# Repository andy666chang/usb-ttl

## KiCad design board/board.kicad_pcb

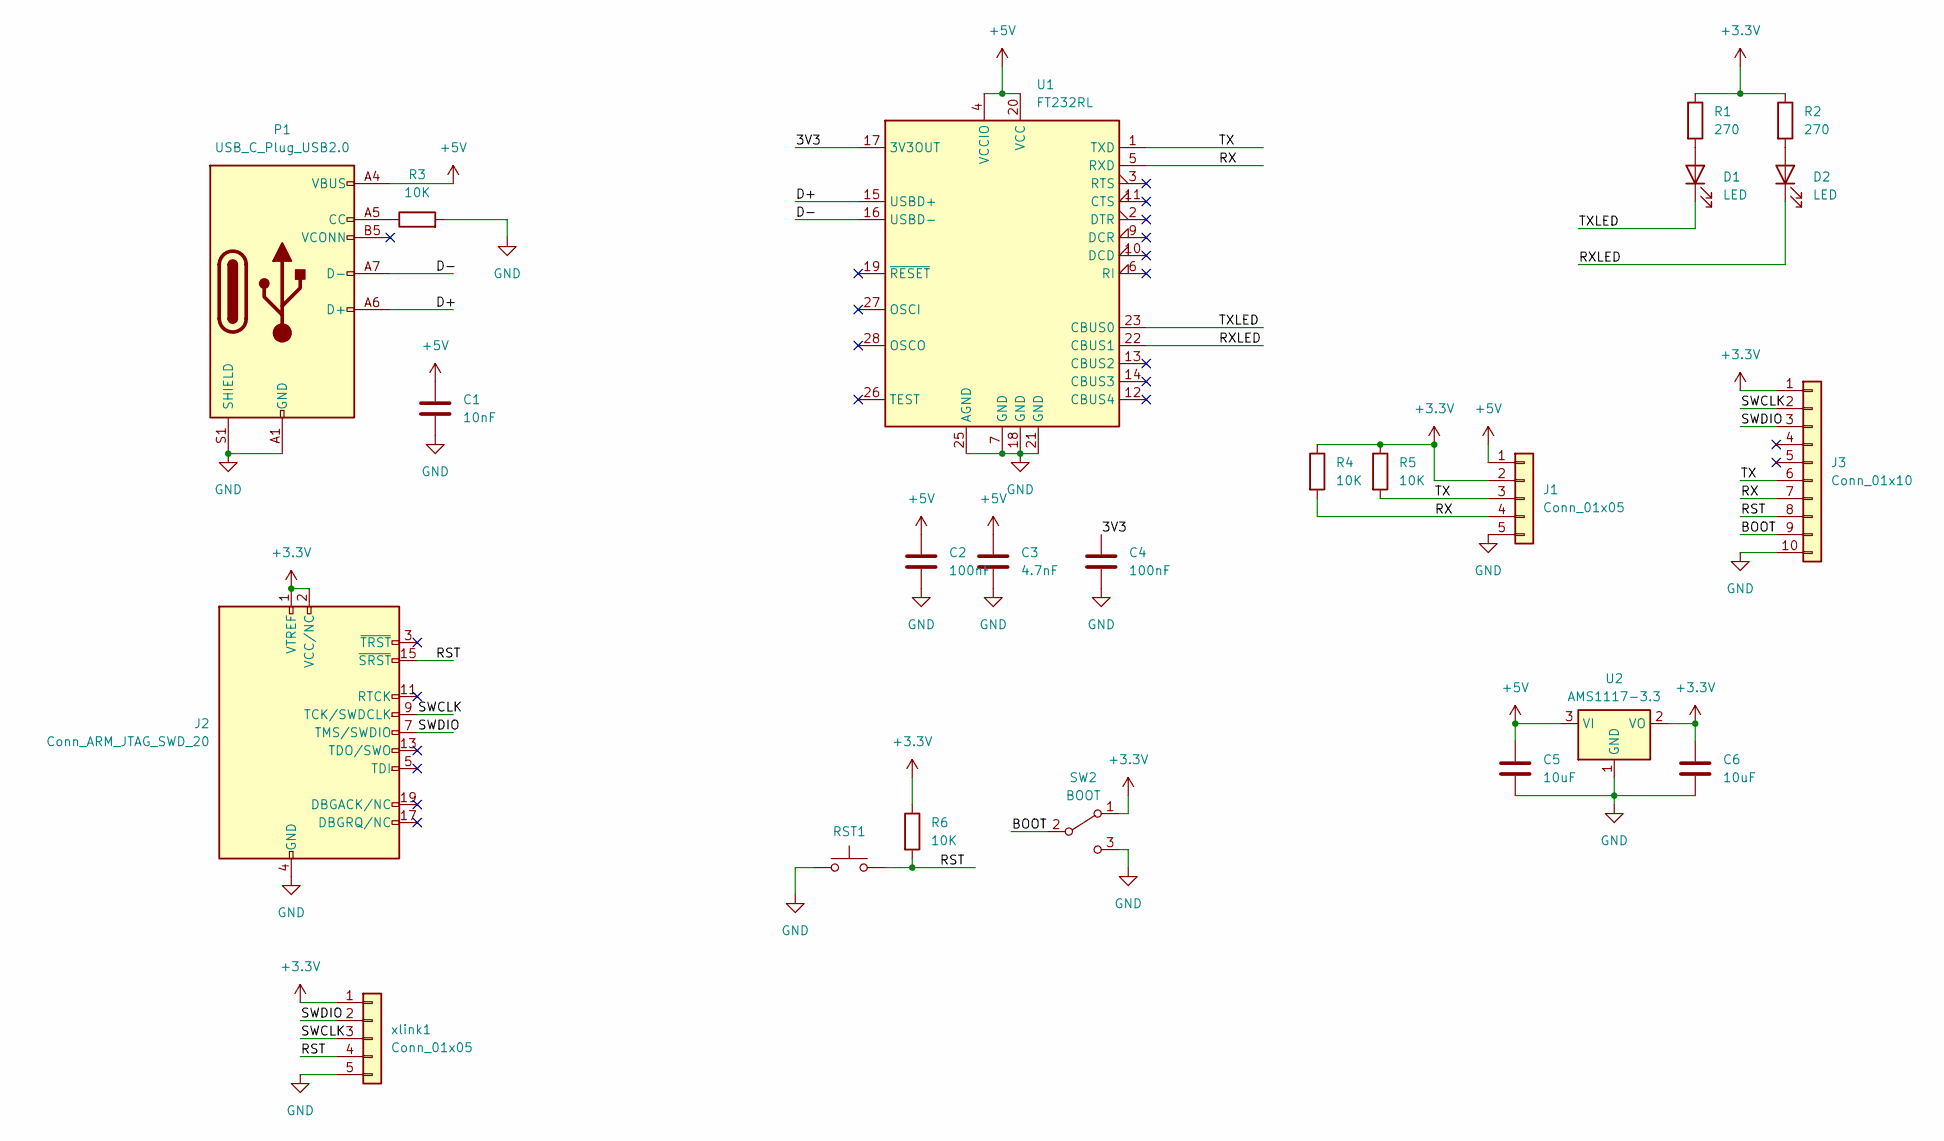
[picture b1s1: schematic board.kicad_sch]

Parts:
C1: 10nF; C_0402_1005Metric_Pad0.74x0.62mm_HandSolder
C2, C4: 100nF; C_0402_1005Metric_Pad0.74x0.62mm_HandSolder
C3: 4.7nF; C_0402_1005Metric_Pad0.74x0.62mm_HandSolder
C5, C6: 10uF; C_0402_1005Metric_Pad0.74x0.62mm_HandSolder
D1, D2: LED; LED_0402_1005Metric_Pad0.77x0.64mm_HandSolder
J1: Conn_01x05; PinHeader_1x05_P2.54mm_Horizontal
J2: Conn_ARM_JTAG_SWD_20; IDC-Header_2x10_P2.54mm_Vertical
J3: Conn_01x10; Molex_54548-1071_1x10-1MP_P0.5mm_Horizontal; JLC C127355 5034801000
P1: USB_C_Plug_USB2.0; USB_C_Receptacle_GCT_USB4105-xx-A_16P_TopMnt_Horizontal; JLCPCB USB-TYPE-C-018 C2927038
R1, R2: 270; R_0402_1005Metric_Pad0.72x0.64mm_HandSolder
R3, R4, R5, R6: 10K; R_0402_1005Metric_Pad0.72x0.64mm_HandSolder
RST1: RST; SW_SPST_Omron_B3FS-100xP
SW2: BOOT; SW_SPDT_CK-JS102011SAQN
U1: FT232RL; SSOP-28_5.3x10.2mm_P0.65mm
U2: AMS1117-3.3; SOT-223-3_TabPin2
xlink1: Conn_01x05; PinHeader_1x05_P2.54mm_Vertical

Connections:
+3.3V: C6.1, J1.2, J2.1 (VTREF), J2.2 (VCC/NC), J3.1, R1.1, R2.1, R4.1, R5.1, R6.1, SW2.1 (A), U2.2 (VO), xlink1.1
+5V: C1.1, C2.1, C3.1, C5.1, J1.1, P1.A4 (VBUS), P1.A9 (VBUS), P1.B4 (VBUS), P1.B9 (VBUS), U1.4 (VCCIO), U1.20 (VCC), U2.3 (VI)
/3V3: C4.1, U1.17 (3V3OUT)
/BOOT: J3.9, SW2.2 (B)
/D+: P1.A6 (D+), U1.15 (USBD+)
/D-: P1.A7 (D-), U1.16 (USBD-)
/RST: J2.15 (~SRST), J3.8, R6.2, RST1.2, xlink1.4
/RX: J1.4, J3.7, R4.2, U1.5 (RXD)
/RXLED: D2.1 (K), U1.22 (CBUS1)
/SWCLK: J2.9 (TCK/SWDCLK), J3.2, xlink1.3
/SWDIO: J2.7 (TMS/SWDIO), J3.3, xlink1.2
/TX: J1.3, J3.6, R5.2, U1.1 (TXD)
/TXLED: D1.1 (K), U1.23 (CBUS0)
GND: C1.2, C2.2, C3.2, C4.2, C5.2, C6.2, J1.5, J2.4 (GND), J2.6 (GND), J2.8 (GND), J2.10 (GND), J2.12 (GND), J2.14 (GND), J2.16 (GND), J2.18 (GND), J2.20 (GND), J3.10, P1.A1 (GND), P1.A12 (GND), P1.B1 (GND), P1.B12 (GND), P1.S1 (SHIELD), R3.2, RST1.1, SW2.3 (C), U1.7 (GND), U1.18 (GND), U1.21 (GND), U1.25 (AGND), U2.1 (GND), xlink1.5
unnamed: D1.2 (A), R1.2
unnamed: D2.2 (A), R2.2
unnamed: P1.A5 (CC), R3.1

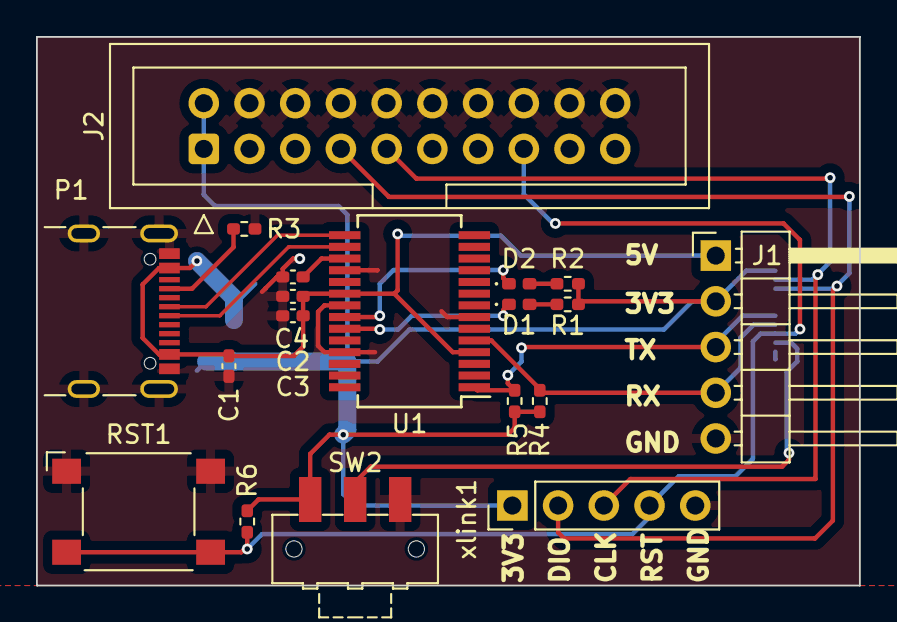
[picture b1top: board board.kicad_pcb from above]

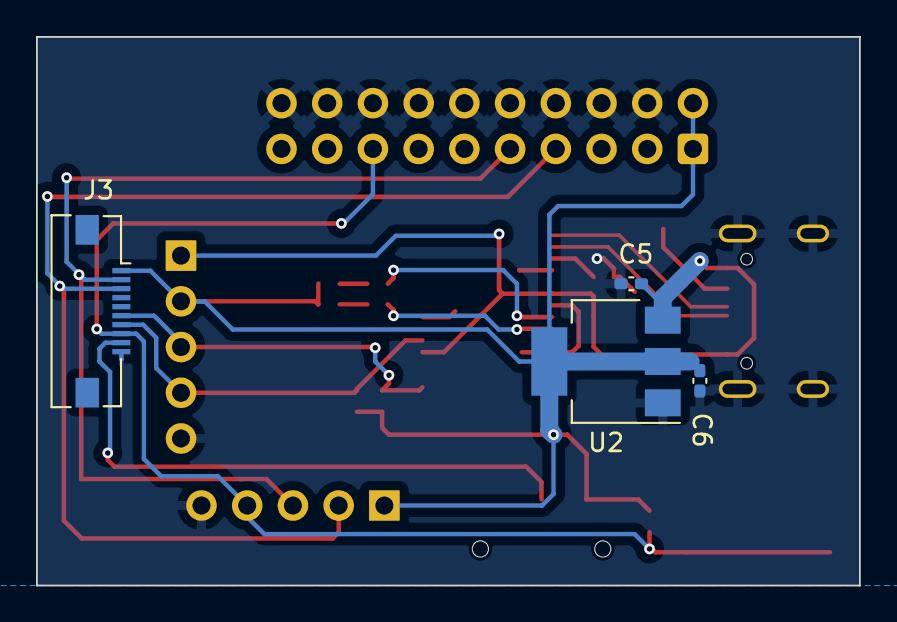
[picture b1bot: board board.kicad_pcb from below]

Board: 2 copper layers, 45.7 x 30.5 mm, 23 parts (4 on the bottom side), 17 nets.

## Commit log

2023-12-19 feat(bsp/usb-ttl): schematic
2023-12-19 feat(bsp/usb-ttl/debug): schematic
2023-12-19 feat(bsp/usb-ttl/debug): pcb layer
    aa
